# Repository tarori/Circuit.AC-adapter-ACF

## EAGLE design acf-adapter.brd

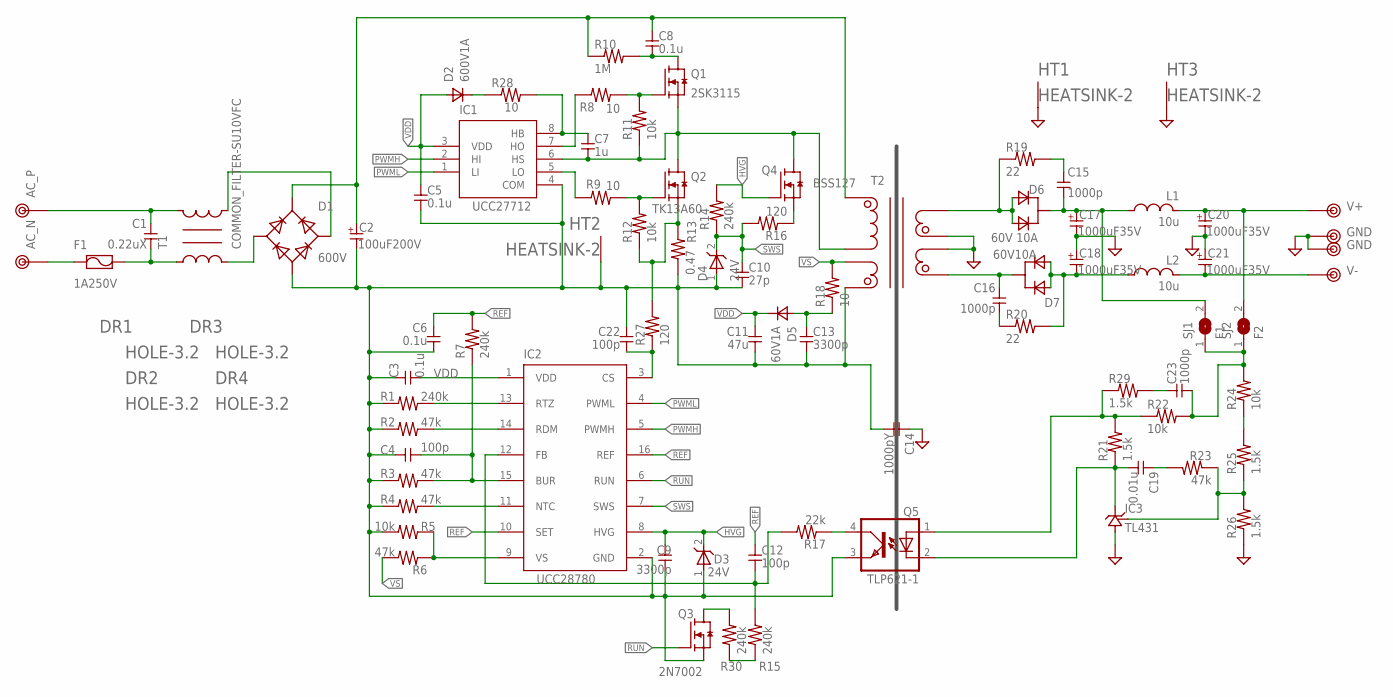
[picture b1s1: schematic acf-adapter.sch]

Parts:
C1: 0.22uX; X-CAPACITER
C2: 100uF200V; E5-10,5A2
C3, C5, C6: 0.1u; 1608
C4, C12, C22: 100p; 1608
C7: 1u; 1608
C8: 0.1u; C075
C9, C13: 3300p; 1608
C10: 27p; 1608
C11: 47u; 2012
C14: 1000pY; Y-CAPACITER
C15, C16, C23: 1000p; 1608
C17, C18, C20, C21: 1000uF35V; E5-10
C19: 0.01u; 1608
D1: 600V; GBU8A
D2: 600V1A; D0204/7
D3, D4: 24V; SOD123
D5: 60V1A; D0204/7
D6: 60V 10A; TO-220
D7: 60V10A; TO-220
DR1, DR2, DR3, DR4: HOLE-3.2; HOLE_3.2
F1: 1A250V; FUSE-5
HT1, HT2, HT3: HEATSINK-2; HEATSINK2
IC1: UCC27712; SOP8
IC2: UCC28780; SO16
IC3: TL431; TO-92
L1, L2: 10u; L5-7,5
Q1: 2SK3115; TO-220
Q2: TK13A60; TO-220
Q3: 2N7002; SC59
Q4: BSS127; SC59
Q5: TLP621-1; DIL04
R1, R7, R14, R15, R30: 240k; 1608
R2, R3, R4, R6, R23: 47k; 1608
R5, R11, R12, R22, R24: 10k; 1608
R8, R9: 10; 2012
R10: 1M; 0204/7
R13: 0.47; 0207/10
R16, R27: 120; 1608
R17: 22k; 1608
R18, R28: 10; 1608
R19, R20: 22; 0207/2V
R21, R25, R26, R29: 1.5k; 1608
SJ1: F1; SJ1608
SJ2: F2; SJ1608
T1: COMMON_FILTER-SU10VFC; SU10VFC
T2: TRANSFORMAER_FLYBACK-PQ2620-ACF; BPQ26/20-1112CPFR
TP1: AC_P; TESTPIN-BIG
TP2: AC_N; TESTPIN-BIG
TP3: V+; TESTPIN-BIG
TP4, TP6: GND; TESTPIN-BIG
TP5: V-; TESTPIN-BIG

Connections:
FB: C12.2, IC2.12 (FB), R15.2, R17.2
GND: C14.1, C17.- (2), C18.+ (1), C20.- (2), C21.+ (1), HT1.HT1, HT3.HT1, IC3.2 (GND), R26.1, T2.9 (L3_P), T2.10 (L4_N), TP4.1, TP6.1
HVG: C9.1, D3.2 (C), IC2.8 (HVG), Q4.1 (G), R14.2
unnamed: F1.1, TP2.1
unnamed: C1.2, F1.2, T1.1
unnamed: C1.1, T1.4, TP1.1
unnamed: D1.2 (AC1), T1.2
unnamed: D1.3 (AC2), T1.3
unnamed: C15.2, C17.+ (1), D6.2 (K), L1.2 (1), SJ1.2
unnamed: Q2.1 (G), R9.1, R12.2
unnamed: C15.1, R19.2
unnamed: C23.2, R22.2, R24.2, SJ1.1, SJ2.1
unnamed: C7.1, IC1.8 (HB), R28.2
unnamed: IC1.7 (HO), R8.2
unnamed: Q1.1 (G), R8.1, R11.2
unnamed: C8.2, Q1.2 (D), R10.2
unnamed: IC1.5 (LO), R9.2
unnamed: Q2.3 (S), R12.1, R13.2, R27.2
unnamed: Q4.2 (S), R16.1
unnamed: D6.1 (A1), D6.3 (A2), R19.1, T2.7 (L3_N), T2.8 (L3_N)
unnamed: C16.1, D7.2 (K), T2.11 (L4_P), T2.12 (L4_P)
unnamed: C13.1, D5.1 (A), R18.1
unnamed: IC2.13 (RTZ), R1.1
unnamed: IC2.14 (RDM), R2.1
unnamed: C16.2, R20.1
unnamed: C18.- (2), D7.1 (A1), D7.3 (A2), L2.2 (1), R20.2
unnamed: IC2.11 (NTC), R4.1
unnamed: R24.1, R25.2
unnamed: IC3.1 (REF), R23.1, R25.1, R26.2
unnamed: C19.1, R23.2
unnamed: C19.2, IC3.3 (OUT), Q5.2 (C), R21.1
unnamed: Q5.1 (A), R21.2, R22.1, R29.1
unnamed: C22.2, IC2.3 (CS), R27.1
unnamed: D2.2 (K), R28.1
unnamed: C4.2, IC2.15 (BUR), R3.2, R7.1
unnamed: C23.1, R29.2
unnamed: Q3.3 (D), R30.2
unnamed: Q5.4 (COL), R17.1
unnamed: IC2.9 (VS), R5.1, R6.1
unnamed: R15.1, R30.1
unnamed: C7.2, IC1.6 (HS), Q1.3 (S), Q2.2 (D), Q4.3 (D), R11.1, T2.1 (L1_N)
PGND: C2.- (2), C3.1, C4.1, C5.2, C6.1, C9.2, C10.2, C11.2, C13.2, C14.2, C22.1, D1.4 (V-), D3.1 (A), D4.1 (A), HT2.HT1, IC1.4 (COM), IC2.2 (GND), Q3.2 (S), Q5.3 (EMIT), R1.2, R2.2, R3.1, R4.2, R5.2, R13.1, T2.5 (L2_P)
PWMH: IC1.2 (HI), IC2.5 (PWMH)
PWML: IC1.1 (LI), IC2.4 (PWML)
REF: C6.2, C12.1, IC2.10 (SET), IC2.16 (REF), R7.2
RUN: IC2.6 (RUN), Q3.1 (G)
SWS: C10.1, D4.2 (C), IC2.7 (SWS), R14.1, R16.2
V+: C20.+ (1), L1.1 (2), SJ2.2, TP3.1
V-: C21.- (2), L2.1 (2), TP5.1
VDD: C3.2, C5.1, C11.1, D2.1 (A), D5.2 (K), IC1.3 (VDD), IC2.1 (VDD)
VP: C2.+ (1), C8.1, D1.1 (V+), R10.1, T2.3 (L1_P)
VS: R6.2, R18.2, T2.6 (L2_N)

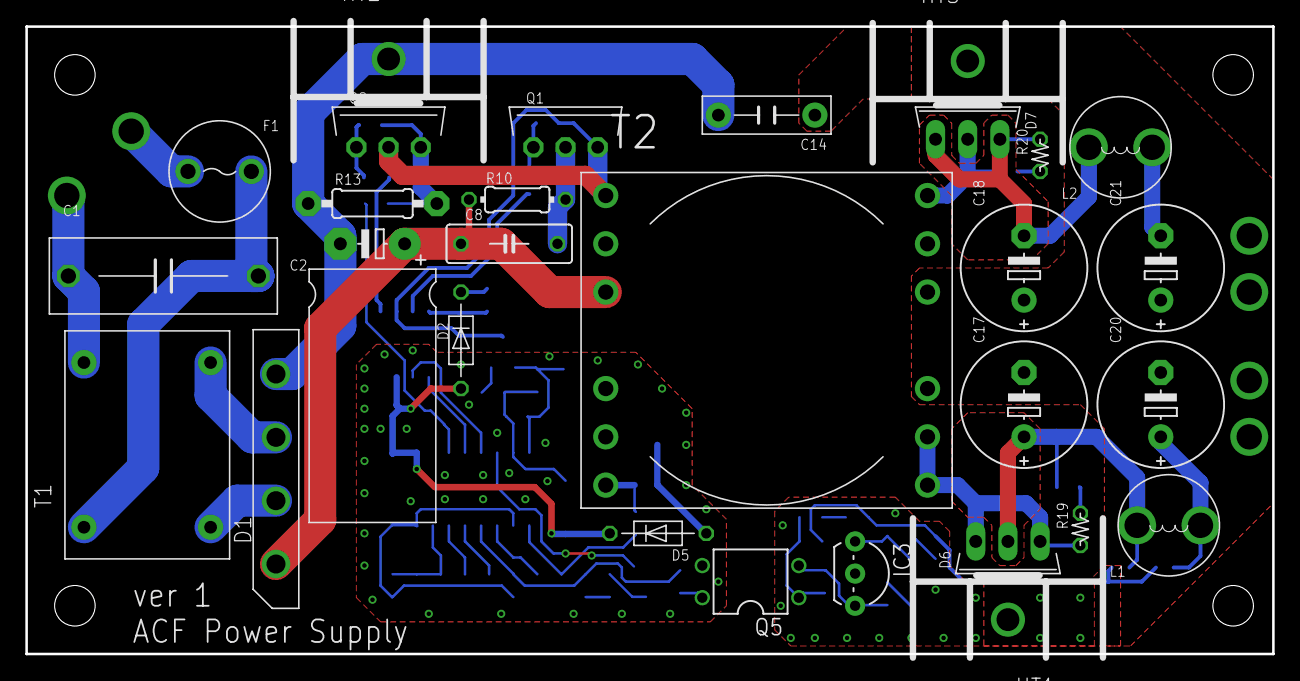
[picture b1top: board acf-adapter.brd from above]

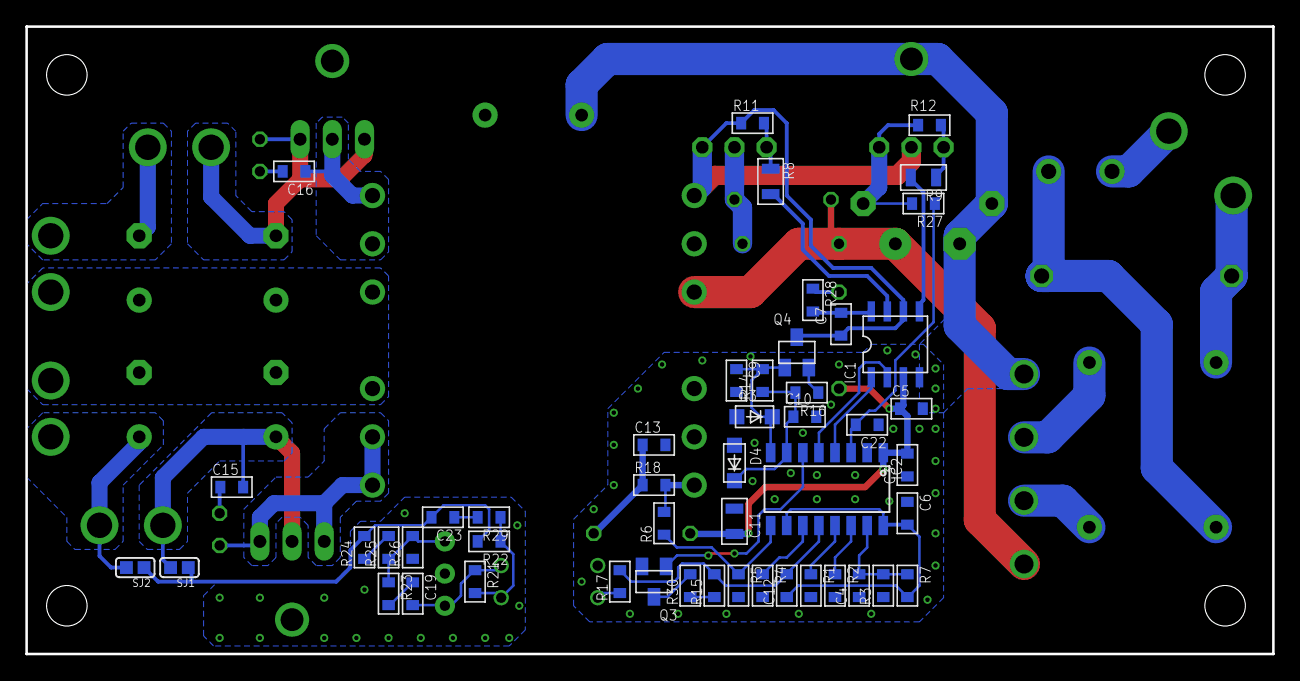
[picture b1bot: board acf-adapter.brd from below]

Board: 2 copper layers, 98.4 x 49.5 mm, 88 parts (49 on the bottom side), 52 nets.

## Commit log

2021-02-04 回路図途中
2021-02-15 回路図できた
2021-02-15 ボード図だいたい
2021-02-15 基板ほぼできた
2021-02-16 Stop追加
